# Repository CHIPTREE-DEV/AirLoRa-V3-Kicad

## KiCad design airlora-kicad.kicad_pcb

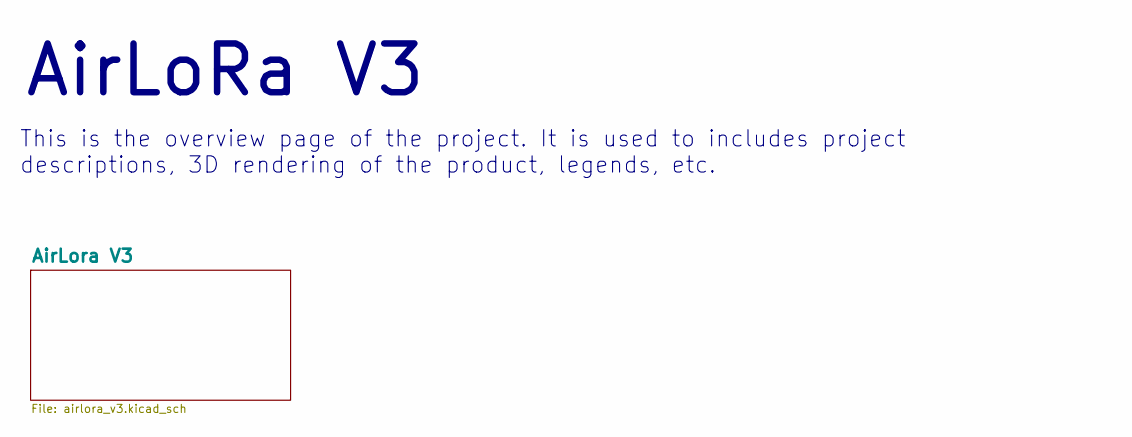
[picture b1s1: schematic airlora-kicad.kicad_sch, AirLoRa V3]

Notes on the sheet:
This is the overview page of the project. It is used to includes project descriptions, 3D rendering of the product, legends, etc.
${TITLE}

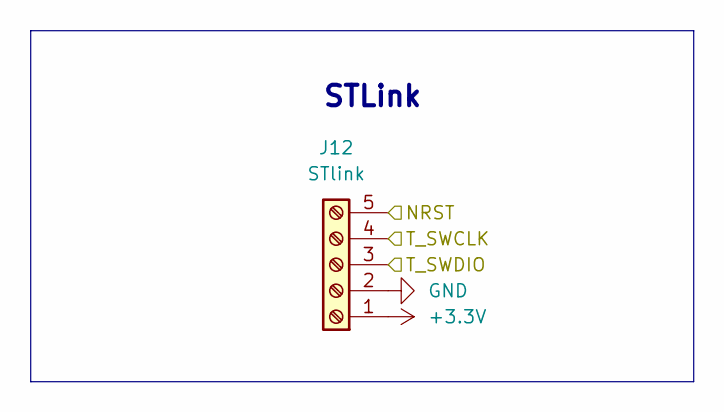
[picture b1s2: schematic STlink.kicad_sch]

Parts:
J12: STlink; JST_XH_B5B-XH-A_1x05_P2.50mm_Vertical

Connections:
+3.3V: J12.1; also elsewhere on the board
/AirLora V3/MCU/NRST: J12.5; also elsewhere on the board
/AirLora V3/MCU/T_SWCLK: J12.4; also elsewhere on the board
/AirLora V3/MCU/T_SWDIO: J12.3; also elsewhere on the board
GND: J12.2; also elsewhere on the board

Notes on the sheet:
STLink

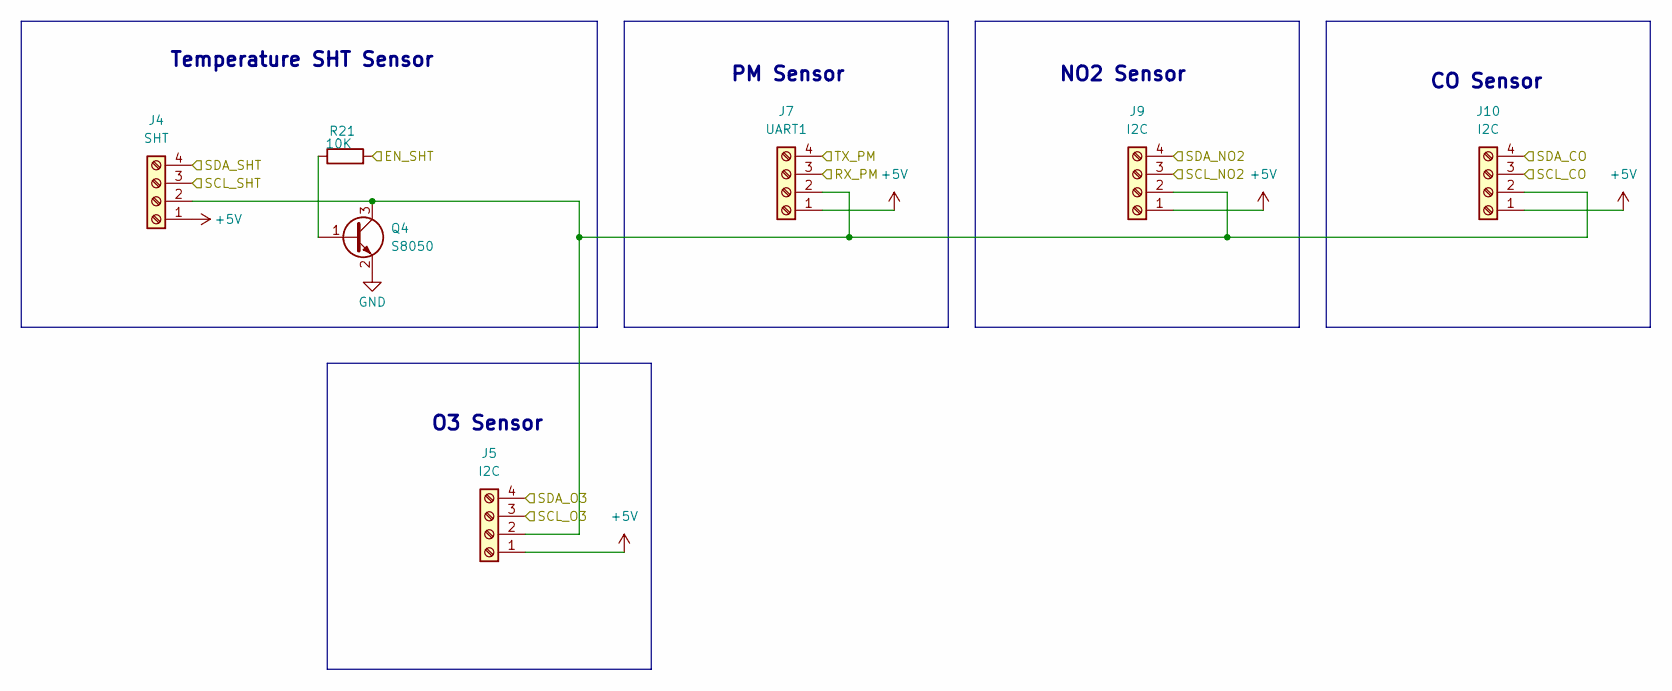
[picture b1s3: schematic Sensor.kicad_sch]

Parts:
J4: SHT; JST_XH_B4B-XH-A_1x04_P2.50mm_Vertical
J5, J9, J10: I2C; Molex_CLIK-Mate_502443-0470_1x04-1MP_P2.00mm_Vertical
J7: UART1; Molex_CLIK-Mate_502443-0470_1x04-1MP_P2.00mm_Vertical
Q4: S8050; SOT-23
R21: 10K; R_0402_1005Metric

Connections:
+5V: J4.1, J5.1, J7.1, J9.1, J10.1; also elsewhere on the board
/AirLora V3/MCU/PB3: R21.2; also elsewhere on the board
/AirLora V3/MCU/SCL2: J4.3, J5.3, J9.3, J10.3; also elsewhere on the board
/AirLora V3/MCU/SDA2: J4.4, J5.4, J9.4, J10.4; also elsewhere on the board
/AirLora V3/MCU/UART1_RX: J7.4; also elsewhere on the board
/AirLora V3/MCU/UART1_TX: J7.3; also elsewhere on the board
GND: Q4.2 (E); also elsewhere on the board
unnamed: J4.2, J5.2, J7.2, J9.2, J10.2, Q4.3 (C)
unnamed: Q4.1 (B), R21.1

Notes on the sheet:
O3 Sensor
NO2 Sensor
PM Sensor
Temperature SHT Sensor
CO Sensor

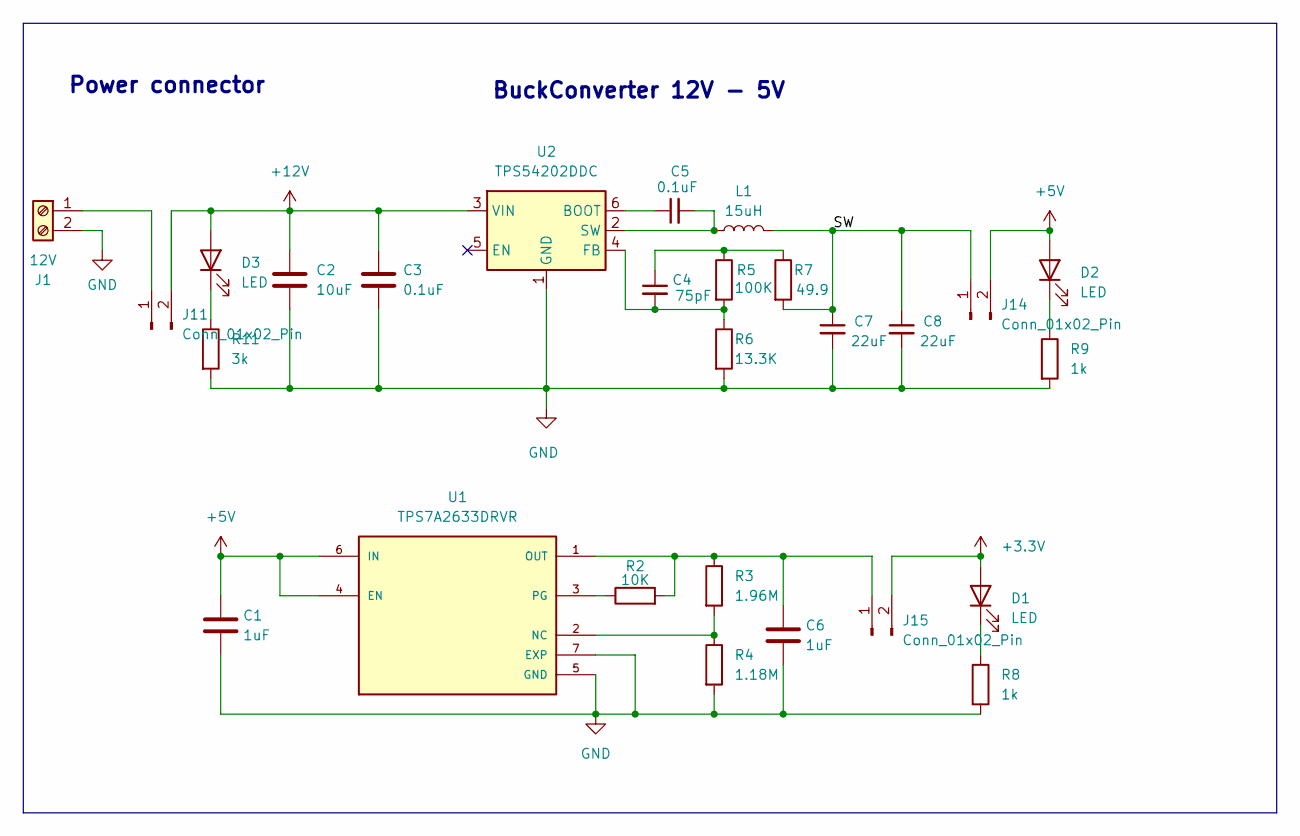
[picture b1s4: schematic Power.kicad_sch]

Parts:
C1, C6: 1uF; C_0805_2012Metric
C2: 10uF; C_1206_3216Metric
C3: 0.1uF; C_0603_1608Metric
C4: 75pF; C_0402_1005Metric
C5: 0.1uF; C_0402_1005Metric
C7, C8: 22uF; C_1206_3216Metric
D1, D2, D3: LED; LED_0603_1608Metric_Pad1.05x0.95mm_HandSolder
J1: 12V; PhoenixContact_MCV_1,5_2-G-3.5_1x02_P3.50mm_Vertical
J11, J14, J15: Conn_01x02_Pin; PinHeader_1x02_P2.54mm_Vertical
L1: 15uH; L_Vishay_IHLP-2020
R2: 10K; R_0402_1005Metric
R3: 1.96M; R_0402_1005Metric
R4: 1.18M; R_0402_1005Metric
R5: 100K; R_0402_1005Metric
R6: 13.3K; R_0402_1005Metric
R7: 49.9; R_0402_1005Metric
R8, R9: 1k; R_0402_1005Metric
R11: 3k; R_0402_1005Metric
U1: TPS7A2633DRVR; LCSC C2876256
U2: TPS54202DDC; SOT-23-6; LCSC C191884

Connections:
+3.3V: D1.2 (A), J15.2; also elsewhere on the board
+5V: C1.1, D2.2 (A), J14.2, U1.4 (EN), U1.6 (IN); also elsewhere on the board
+12V: C2.1, C3.1, D3.2 (A), J11.2, U2.3 (VIN)
/AirLora V3/Power/SW: C7.1, C8.1, J14.1, L1.2, R7.2
GND: C1.2, C2.2, C3.2, C6.2, C7.2, C8.2, J1.2, R4.2, R6.2, R8.2, R9.2, R11.2, U1.5 (GND), U1.7 (EXP), U2.1 (GND); also elsewhere on the board
unnamed: C4.1, R5.1, R7.1
unnamed: D1.1 (K), R8.1
unnamed: D2.1 (K), R9.1
unnamed: D3.1 (K), R11.1
unnamed: J1.1, J11.1
unnamed: C6.1, J15.1, R2.2, R3.1, U1.1 (OUT)
unnamed: R3.2, R4.1, U1.2 (NC)
unnamed: R2.1, U1.3 (PG)
unnamed: C5.1, U2.6 (BOOT)
unnamed: C4.2, R5.2, R6.1, U2.4 (FB)
unnamed: C5.2, L1.1, U2.2 (SW)

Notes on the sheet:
BuckConverter 12V - 5V
Power connector

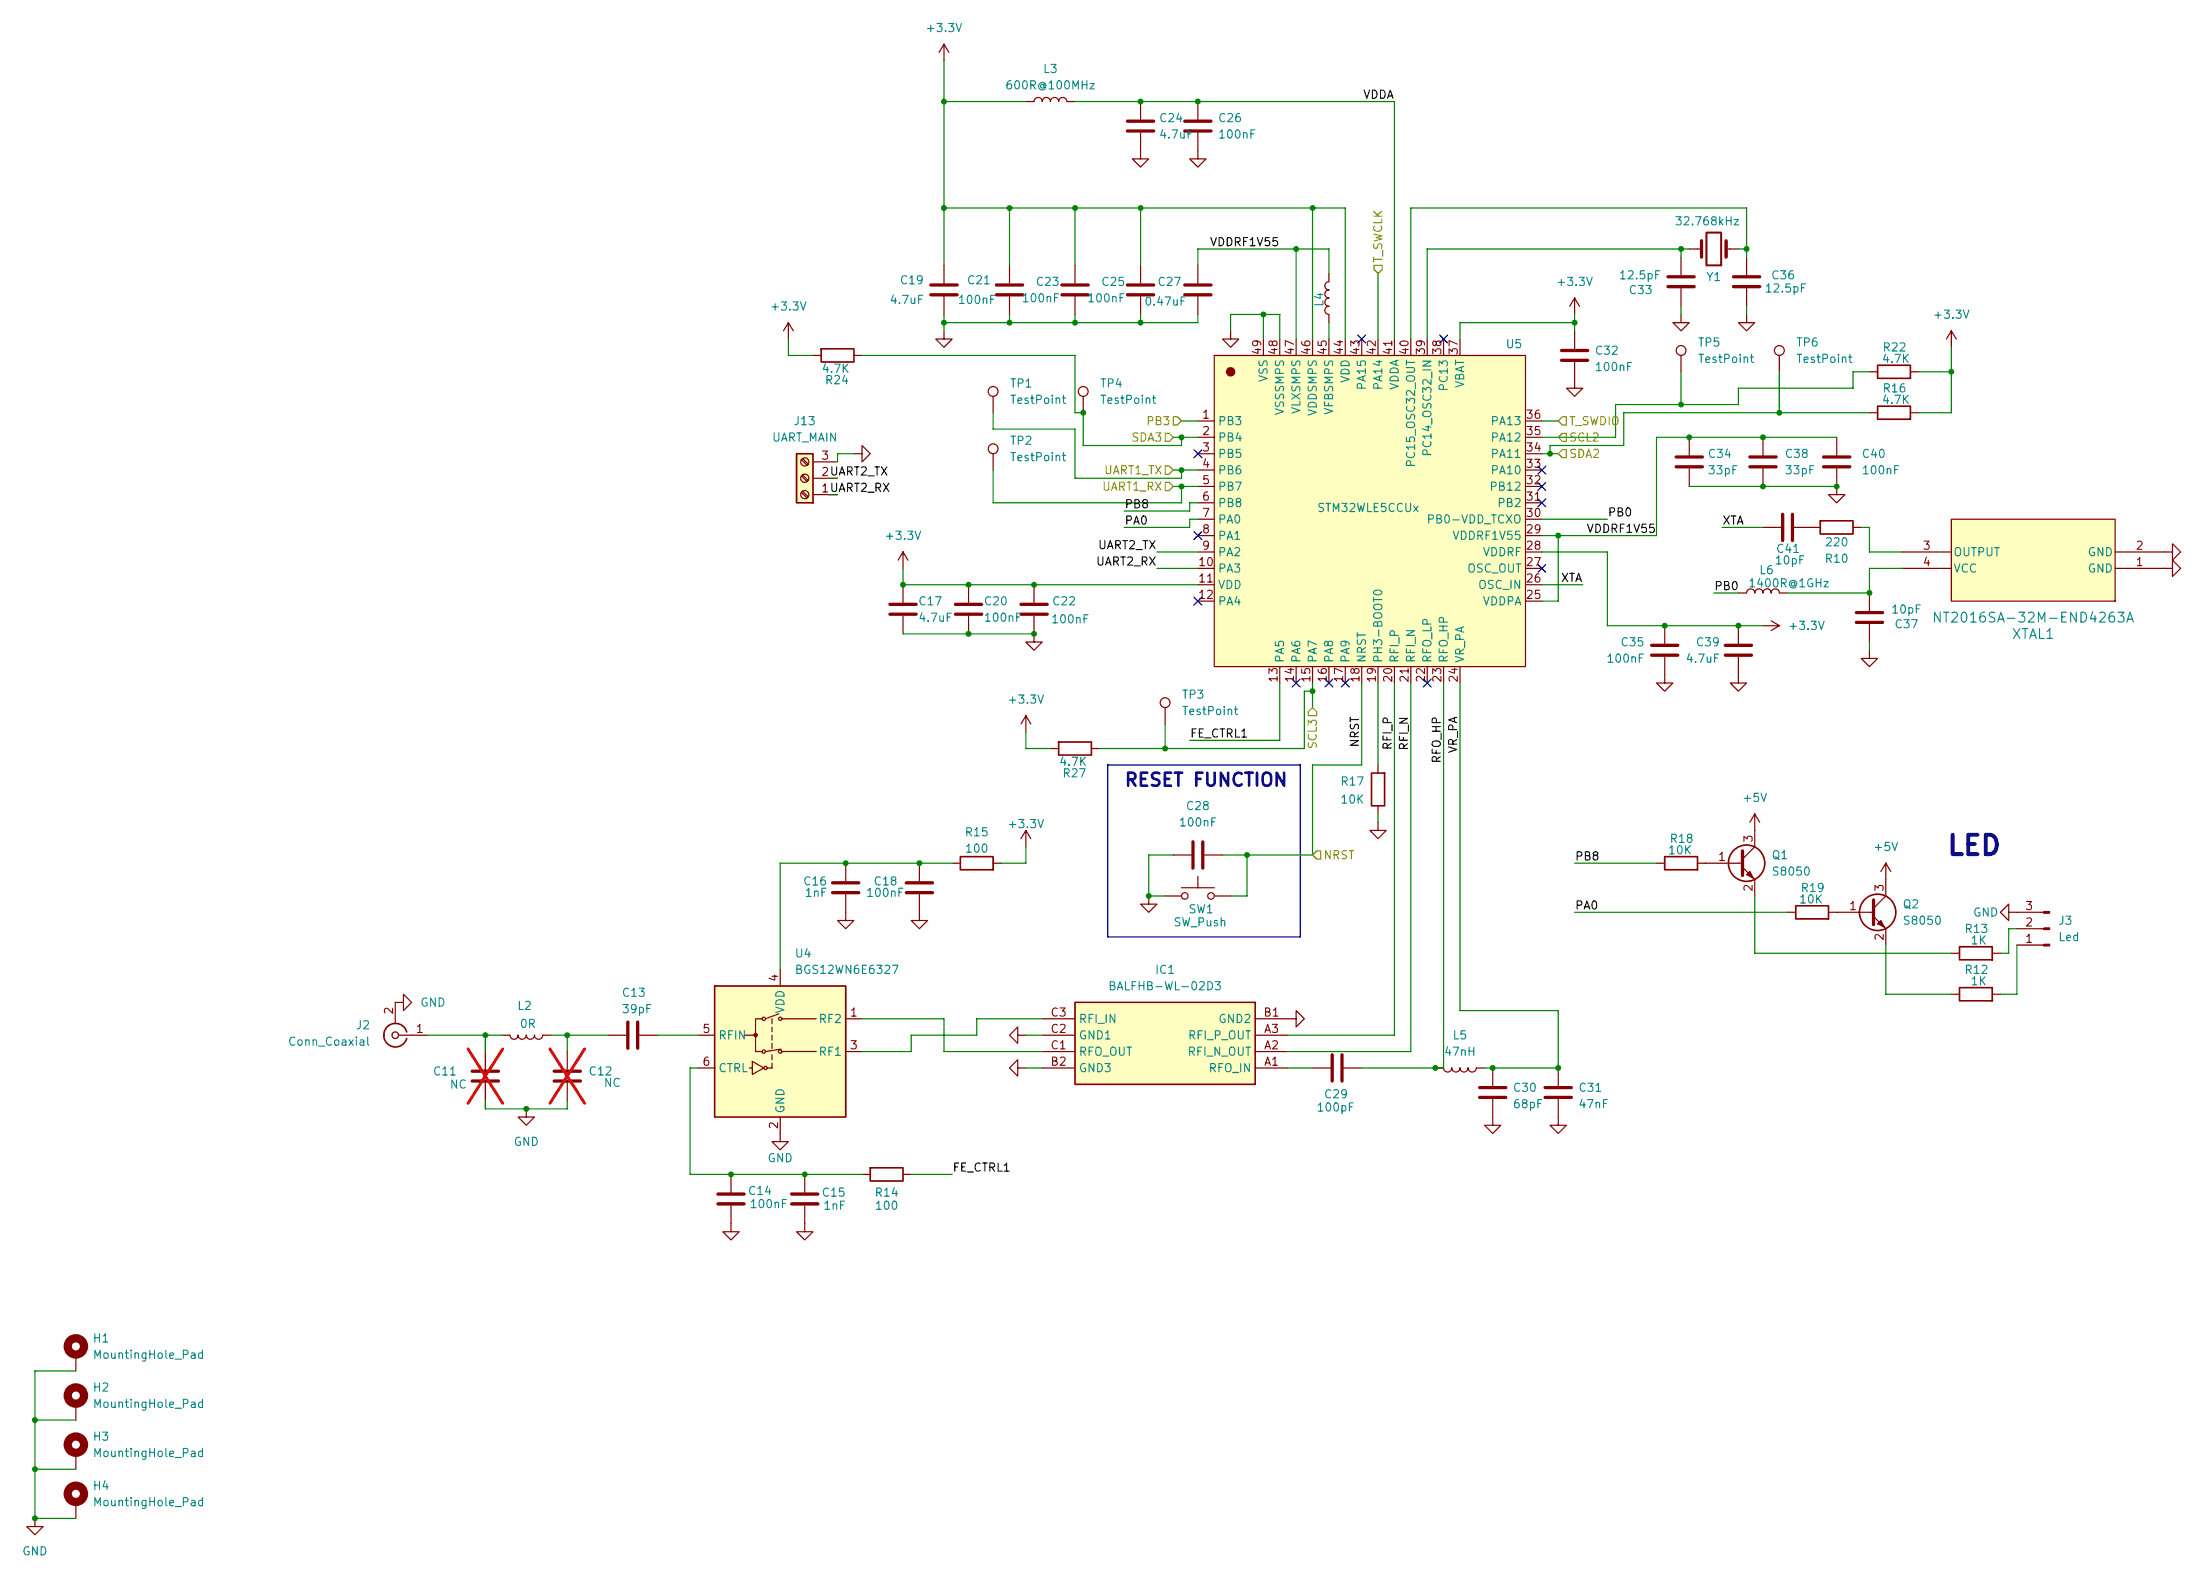
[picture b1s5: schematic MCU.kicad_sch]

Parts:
C11, C12: NC; C_0402_1005Metric; not fitted
C13: 39pF; C_0402_1005Metric
C14, C18, C20, C21, C22, C23, C25, C26, C28, C32, C35, C40: 100nF; C_0402_1005Metric
C15, C16: 1nF; C_0402_1005Metric
C17, C39: 4.7uF; C_0603_1608Metric
C19, C24: 4.7uF; C_0402_1005Metric
C27: 0.47uF; C_0402_1005Metric
C29: 100pF; C_0402_1005Metric
C30: 68pF; C_0402_1005Metric
C31: 47nF; C_0402_1005Metric
C33, C36: 12.5pF; C_0402_1005Metric
C34, C38: 33pF; C_0402_1005Metric
C37, C41: 10pF; C_0402_1005Metric
H1, H2, H3, H4: MountingHole_Pad; MountingHole_3mm_Pad_Via
IC1: BALFHB-WL-02D3; BALFHBWL05D3; Manufacturer_Part_Number BALFHB-WL-05D3; Mouser Part Number 511-BALFHB-WL-05D3
J2: Conn_Coaxial; SMA_Amphenol_132134-11_Vertical
J3: Led; JST_XH_B3B-XH-A_1x03_P2.50mm_Vertical
J13: UART_MAIN; JST_XH_B3B-XH-A_1x03_P2.50mm_Vertical
L2: 0R; L_0402_1005Metric
L3: 600R@100MHz; L_0402_1005Metric
L4: 15uH; C_0805_2012Metric
L5: 47nH; L_0402_1005Metric
L6: 1400R@1GHz; L_0402_1005Metric
Q1, Q2: S8050; SOT-23
R10: 220; R_0402_1005Metric
R12, R13: 1K; R_0603_1608Metric
R14, R15: 100; R_0402_1005Metric
R16, R22, R24, R27: 4.7K; R_0402_1005Metric
R17, R18, R19: 10K; R_0402_1005Metric
SW1: SW_Push; SW_Tactile_SPST_Angled_PTS645Vx39-2LFS
TP1, TP2, TP3, TP4, TP5, TP6: TestPoint; TestPoint_Loop_D1.80mm_Drill1.0mm_Beaded
U4: BGS12WN6E6327; BGS12SN6E6327XTSA1
U5: STM32WLE5CCUx; QFN-48-1EP_7x7mm_P0.5mm_EP5.6x5.6mm
XTAL1: NT2016SA-32M-END4263A; NT2016SA-32M-END4263A_NDK
Y1: 32.768kHz; XTAL_NX2012SA-32.768K-STD-MUB-1

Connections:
+3.3V: C17.1, C19.1, C20.1, C21.2, C22.2, C23.1, C25.1, C32.1, C35.1, C39.1, L3.1, R15.2, R16.2, R22.2, R24.2, R27.2, U5.11 (VDD), U5.28 (VDDRF), U5.37 (VBAT), U5.44 (VDD), U5.46 (VDDSMPS); also elsewhere on the board
+5V: Q1.3 (C), Q2.3 (C); also elsewhere on the board
/AirLora V3/MCU/FE_CTRL1: R14.1, U5.13 (PA5)
/AirLora V3/MCU/NRST: C28.2, SW1.2, U5.18 (NRST); also elsewhere on the board
/AirLora V3/MCU/PA0: R19.1, U5.7 (PA0)
/AirLora V3/MCU/PB0: L6.1, U5.30 (PB0-VDD_TCXO)
/AirLora V3/MCU/PB3: U5.1 (PB3); also elsewhere on the board
/AirLora V3/MCU/PB8: R18.1, U5.6 (PB8)
/AirLora V3/MCU/RFI_N: IC1.A2 (RFI_N_OUT), U5.21 (RFI_N)
/AirLora V3/MCU/RFI_P: IC1.A3 (RFI_P_OUT), U5.20 (RFI_P)
/AirLora V3/MCU/RFO_HP: C29.2, L5.2, U5.23 (RFO_HP)
/AirLora V3/MCU/SCL2: R22.1, TP5.1, U5.35 (PA12); also elsewhere on the board
/AirLora V3/MCU/SCL3: R27.1, TP3.1, U5.15 (PA7)
/AirLora V3/MCU/SDA2: R16.1, TP6.1, U5.34 (PA11); also elsewhere on the board
/AirLora V3/MCU/SDA3: R24.1, TP4.1, U5.2 (PB4)
/AirLora V3/MCU/T_SWCLK: U5.42 (PA14); also elsewhere on the board
/AirLora V3/MCU/T_SWDIO: U5.36 (PA13); also elsewhere on the board
/AirLora V3/MCU/UART1_RX: TP2.1, U5.5 (PB7); also elsewhere on the board
/AirLora V3/MCU/UART1_TX: TP1.1, U5.4 (PB6); also elsewhere on the board
/AirLora V3/MCU/UART2_RX: J13.1, U5.10 (PA3)
/AirLora V3/MCU/UART2_TX: J13.2, U5.9 (PA2)
/AirLora V3/MCU/VDDA: C24.1, C26.1, L3.2, U5.41 (VDDA)
/AirLora V3/MCU/VDDRF1V55: C27.1, C34.1, C38.1, C40.1, L4.2, U5.25 (VDDPA), U5.29 (VDDRF1V55), U5.47 (VLXSMPS)
/AirLora V3/MCU/VR_PA: C30.1, C31.1, L5.1, U5.24 (VR_PA)
/AirLora V3/MCU/XTA: C41.1, U5.26 (OSC_IN)
GND: C11.1, C12.1, C14.2, C15.2, C16.1, C17.2, C18.1, C19.2, C20.2, C21.1, C22.1, C23.2, C24.2, C25.2, C26.2, C27.2, C28.1, C30.2, C31.2, C32.2, C33.2, C34.2, C35.2, C36.1, C37.2, C38.2, C39.2, C40.2, H1.1, H2.1, H3.1, H4.1, IC1.B1 (GND2), IC1.B2 (GND3), IC1.C2 (GND1), J2.2 (Ext), J3.3, J13.3, R17.1, SW1.1, U4.2 (GND), U5.48 (VSSSMPS), U5.49 (VSS), XTAL1.1 (GND), XTAL1.2 (GND); also elsewhere on the board
unnamed: C12.2, C13.2, L2.1
unnamed: C41.2, R10.2
unnamed: IC1.C3 (RFI_IN), U4.3 (RF1)
unnamed: C29.1, IC1.A1 (RFO_IN)
unnamed: IC1.C1 (RFO_OUT), U4.1 (RF2)
unnamed: C11.2, J2.1 (In), L2.2
unnamed: J3.1, R12.2
unnamed: J3.2, R13.2
unnamed: Q1.1 (B), R18.2
unnamed: Q1.2 (E), R13.1
unnamed: Q2.1 (B), R19.2
unnamed: Q2.2 (E), R12.1
unnamed: C14.1, C15.1, R14.2, U4.6 (CTRL)
unnamed: C13.1, U4.5 (RFIN)
unnamed: C16.2, C18.2, R15.1, U4.4 (VDD)
unnamed: C33.1, U5.39 (PC14_OSC32_IN), Y1.2
unnamed: C36.2, U5.40 (PC15_OSC32_OUT), Y1.1
unnamed: R17.2, U5.19 (PH3-BOOT0)
unnamed: L4.1, U5.45 (VFBSMPS)
unnamed: R10.1, XTAL1.3 (OUTPUT)
unnamed: C37.1, L6.2, XTAL1.4 (VCC)

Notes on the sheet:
RESET FUNCTION
LED

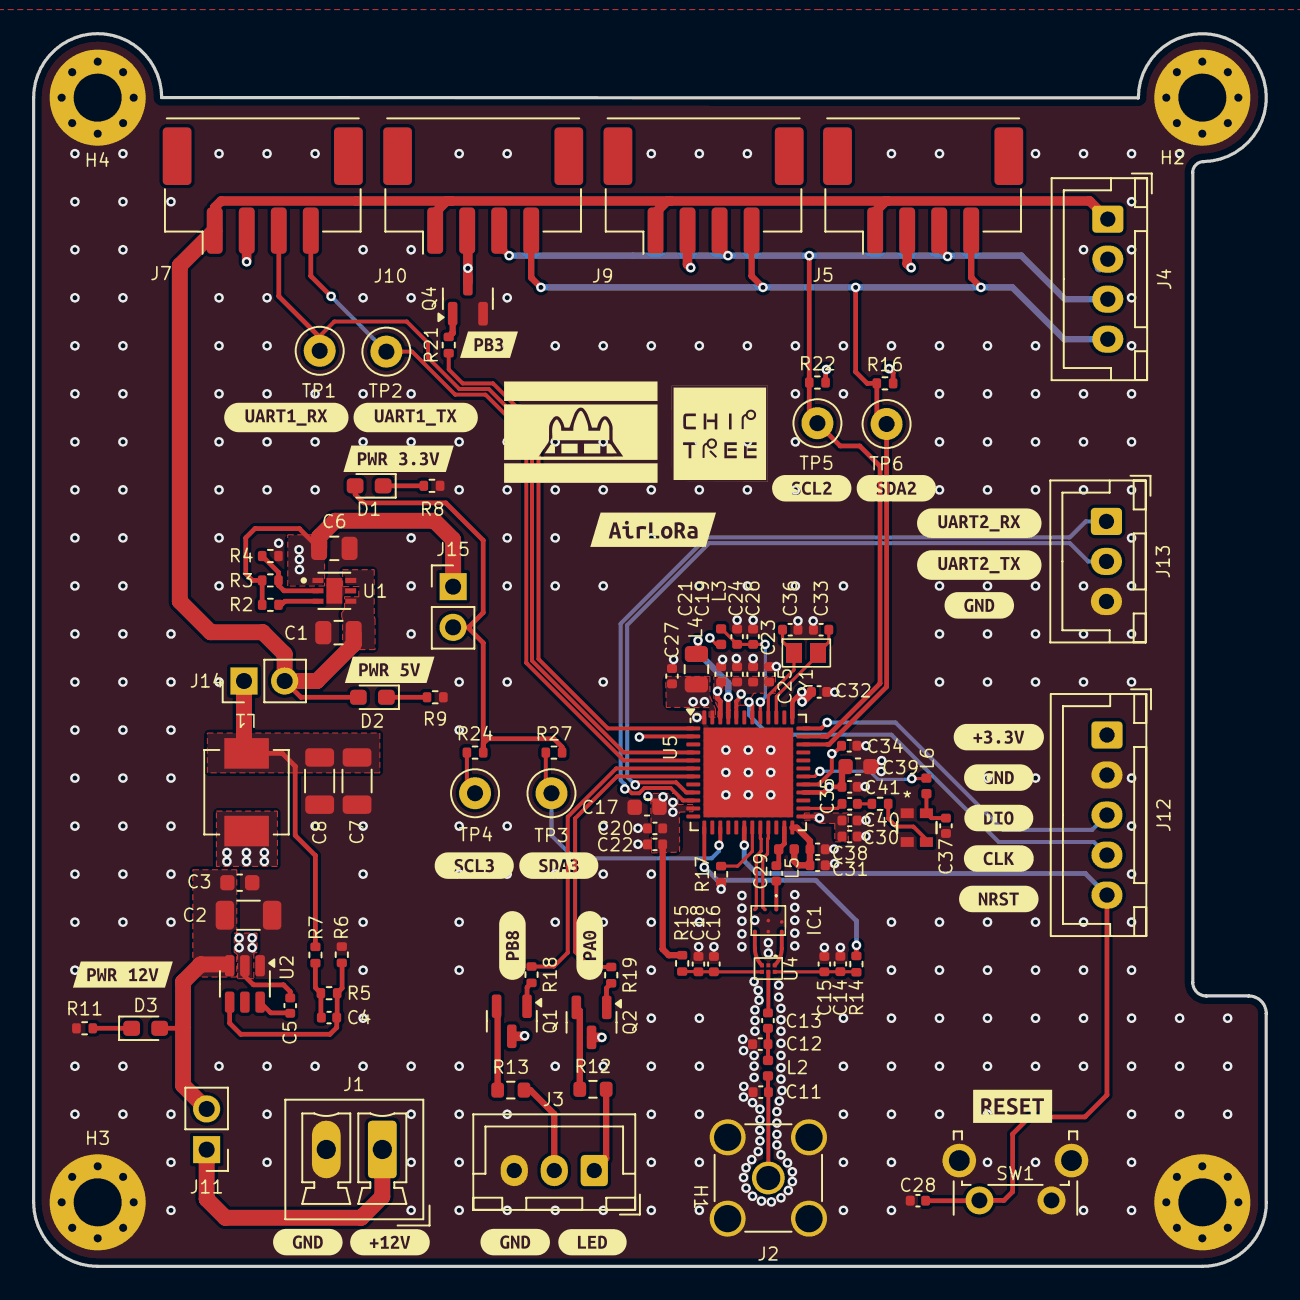
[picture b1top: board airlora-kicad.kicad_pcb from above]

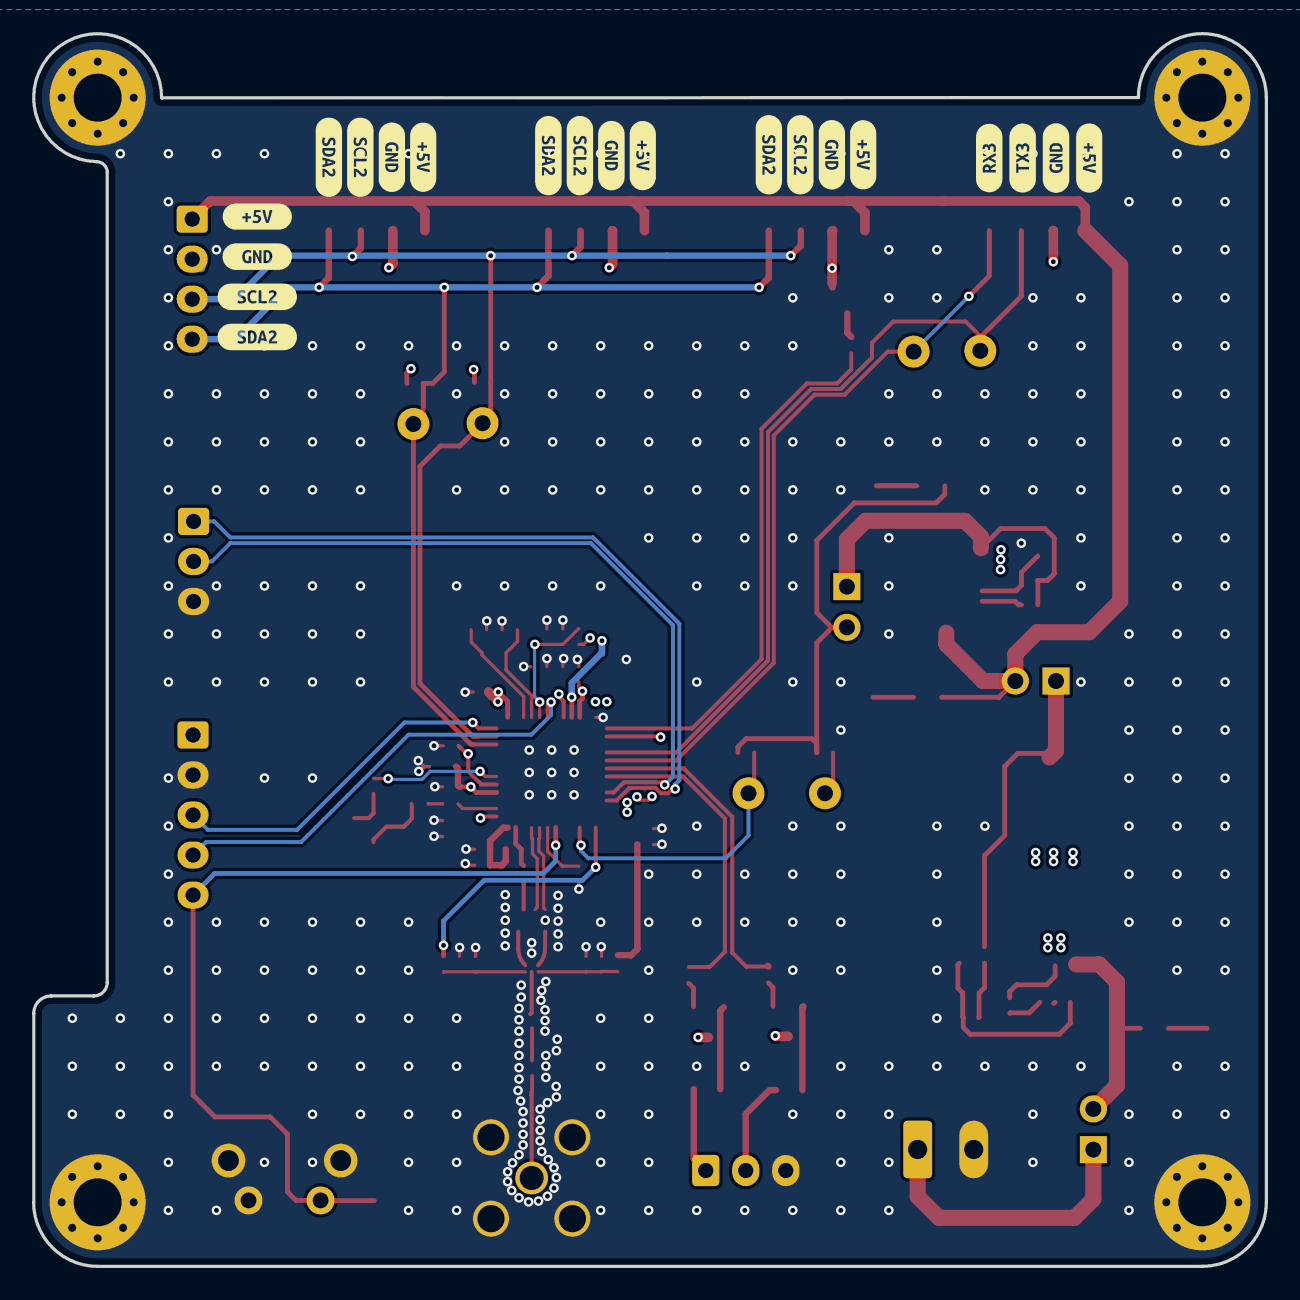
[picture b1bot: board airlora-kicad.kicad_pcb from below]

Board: 4 copper layers, 77.0 x 77.0 mm, 150 parts (20 on the bottom side), 62 nets.

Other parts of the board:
kibuzzard-66A700A1: G***; kibuzzard-66A700A1
kibuzzard-66A704F7: G***; kibuzzard-66A704F7
kibuzzard-66A704FE, kibuzzard-66A704FE#2: G***; kibuzzard-66A704FE
kibuzzard-66A705CB: G***; kibuzzard-66A705CB
kibuzzard-66A705D3: G***; kibuzzard-66A705D3
kibuzzard-66A7008A: G***; kibuzzard-66A7008A
kibuzzard-66A7052C: G***; kibuzzard-66A7052C
kibuzzard-66A7121E: G***; kibuzzard-66A7121E
kibuzzard-66A7130C: G***; kibuzzard-66A7130C
kibuzzard-66A47256: G***; kibuzzard-66A47256
kibuzzard-66A70081: G***; kibuzzard-66A70081
kibuzzard-66A70091: G***; kibuzzard-66A70091
kibuzzard-66A70098: G***; kibuzzard-66A70098
kibuzzard-66A70504, kibuzzard-66A70504#2: G***; kibuzzard-66A70504
kibuzzard-66A70534: G***; kibuzzard-66A70534
kibuzzard-66A71226: G***; kibuzzard-66A71226
kibuzzard-66A71314: G***; kibuzzard-66A71314
kibuzzard-66A71938: G***; kibuzzard-66A71938
kibuzzard-6690D08F: G***; kibuzzard-6690D08F
kibuzzard-66763AB2: G***; kibuzzard-66763AB2
kibuzzard-66763ACD: G***; kibuzzard-66763ACD
kibuzzard-667540EB, kibuzzard-667540EB#2, kibuzzard-667540EB#3, kibuzzard-667540EB#4, kibuzzard-667540EB#5: G***; kibuzzard-667540EB
kibuzzard-667541A7: G***; kibuzzard-667541A7
kibuzzard-667541BE: G***; kibuzzard-667541BE
kibuzzard-667541C9: G***; kibuzzard-667541C9
kibuzzard-6679349C: G***; kibuzzard-6679349C
kibuzzard-66752922, kibuzzard-66752922#2, kibuzzard-66752922#3, kibuzzard-66752922#4, kibuzzard-66752922#5, kibuzzard-66752922#6, kibuzzard-66752922#7, kibuzzard-66752922#8, kibuzzard-66752922#9: G***; kibuzzard-66752922
kibuzzard-66752939: G***; kibuzzard-66752939
kibuzzard-66752971: G***; kibuzzard-66752971
kibuzzard-66752981: G***; kibuzzard-66752981
kibuzzard-66753395: G***; kibuzzard-66753395
kibuzzard-66754176: G***; kibuzzard-66754176

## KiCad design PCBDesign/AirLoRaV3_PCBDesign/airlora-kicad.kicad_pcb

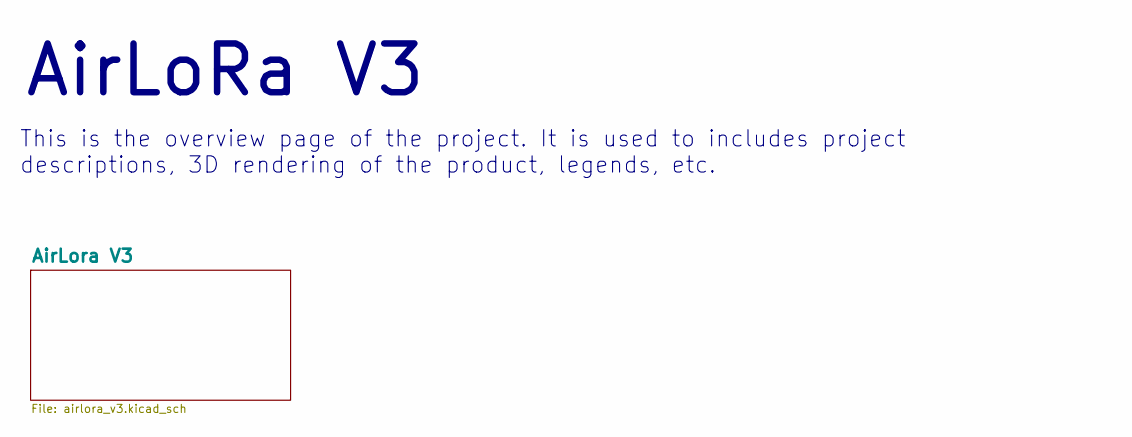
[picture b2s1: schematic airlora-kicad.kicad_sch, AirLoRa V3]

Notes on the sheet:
This is the overview page of the project. It is used to includes project descriptions, 3D rendering of the product, legends, etc.
${TITLE}

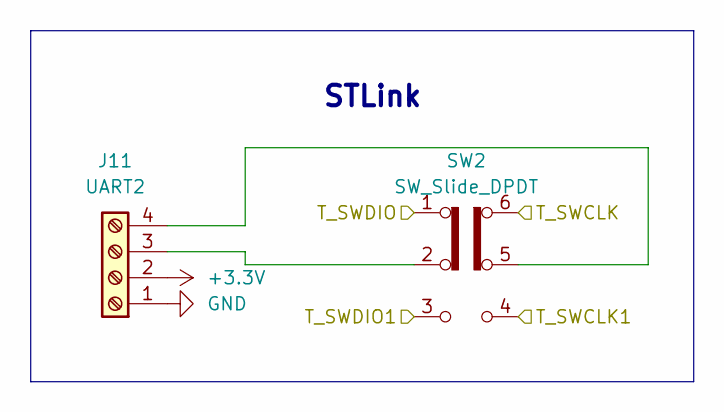
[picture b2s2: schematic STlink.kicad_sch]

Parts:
J11: UART2; JST_XH_B4B-XH-A_1x04_P2.50mm_Vertical
SW2: SW_Slide_DPDT; SW_E-Switch_EG1271_SPDT

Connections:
+3.3V: J11.2; also elsewhere on the board
/AirLora V3/MCU Sub/SW_CLK: SW2.4 (A); also elsewhere on the board
/AirLora V3/MCU Sub/SW_DIO: SW2.3 (C); also elsewhere on the board
/AirLora V3/MCU/T_SWCLK: SW2.6 (C); also elsewhere on the board
/AirLora V3/MCU/T_SWDIO: SW2.1 (A); also elsewhere on the board
GND: J11.1; also elsewhere on the board
unnamed: J11.3, SW2.2 (B)
unnamed: J11.4, SW2.5 (B)

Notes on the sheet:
STLink

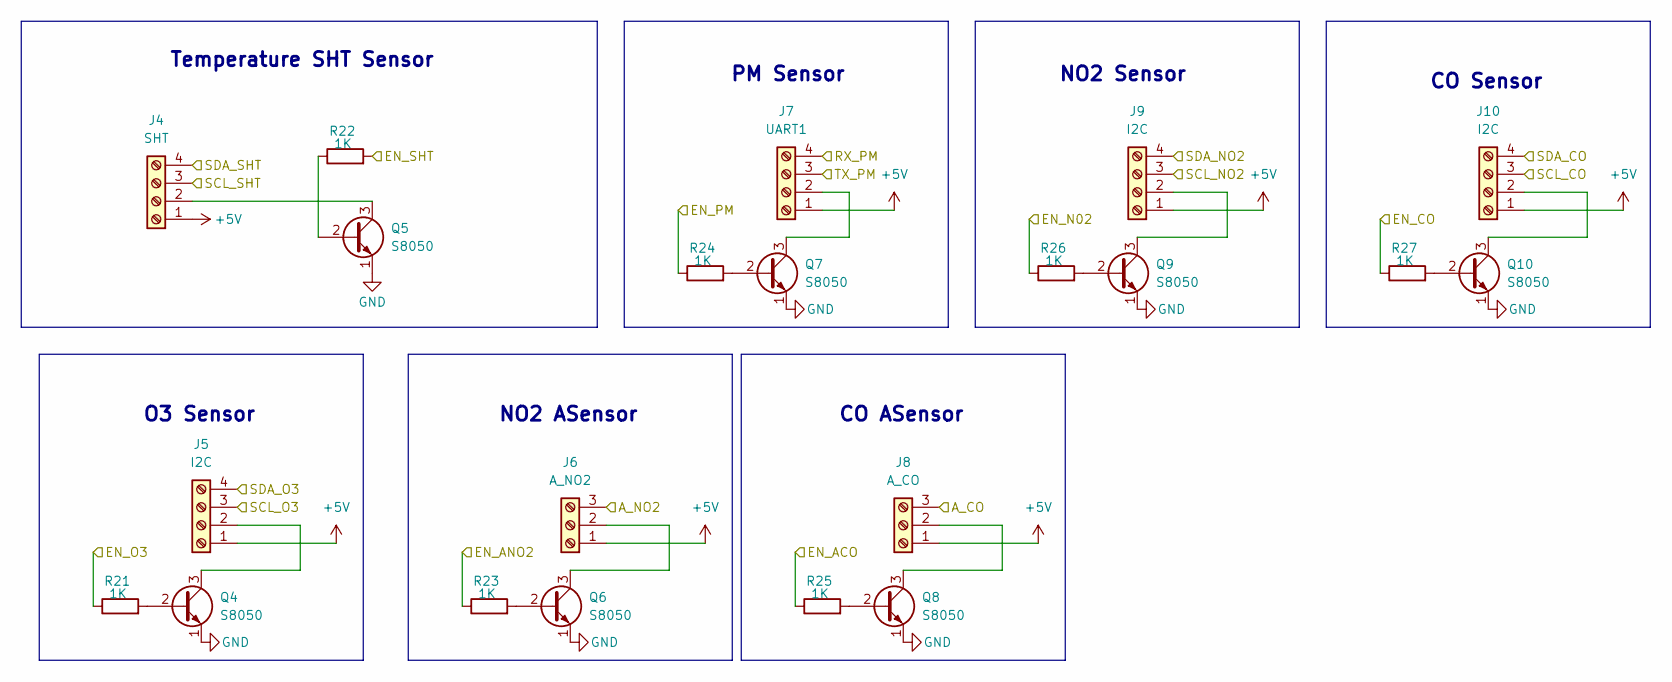
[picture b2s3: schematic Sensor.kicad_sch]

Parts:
J4: SHT; JST_XH_B4B-XH-A_1x04_P2.50mm_Vertical
J5, J9, J10: I2C; Molex_CLIK-Mate_502585-0470_1x04-1MP_P1.50mm_Horizontal
J6: A_NO2; JST_XH_B3B-XH-A_1x03_P2.50mm_Vertical
J7: UART1; Molex_CLIK-Mate_502585-0470_1x04-1MP_P1.50mm_Horizontal
J8: A_CO; JST_XH_B3B-XH-A_1x03_P2.50mm_Vertical
Q4, Q5, Q6, Q7, Q8, Q9, Q10: S8050; SOT-23
R21, R22, R23, R24, R25, R26, R27: 1K; R_0402_1005Metric_Pad0.72x0.64mm_HandSolder

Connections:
+5V: J4.1, J5.1, J6.1, J7.1, J8.1, J9.1, J10.1; also elsewhere on the board
/AirLora V3/MCU Sub/PA4: R25.1; also elsewhere on the board
/AirLora V3/MCU Sub/PA5: R24.1; also elsewhere on the board
/AirLora V3/MCU Sub/PA6: R23.1; also elsewhere on the board
/AirLora V3/MCU Sub/PA7: R22.2; also elsewhere on the board
/AirLora V3/MCU Sub/PA15: R21.1; also elsewhere on the board
/AirLora V3/MCU Sub/PB0: J6.3; also elsewhere on the board
/AirLora V3/MCU Sub/PB1: J8.3; also elsewhere on the board
/AirLora V3/MCU Sub/PB3: R26.1; also elsewhere on the board
/AirLora V3/MCU Sub/PB4: R27.1; also elsewhere on the board
/AirLora V3/MCU Sub/RX3: J7.3; also elsewhere on the board
/AirLora V3/MCU Sub/SCL1: J4.3, J5.3, J9.3, J10.3; also elsewhere on the board
/AirLora V3/MCU Sub/SDA1: J4.4, J5.4, J9.4, J10.4; also elsewhere on the board
/AirLora V3/MCU Sub/TX3: J7.4; also elsewhere on the board
GND: Q4.1 (E), Q5.1 (E), Q6.1 (E), Q7.1 (E), Q8.1 (E), Q9.1 (E), Q10.1 (E); also elsewhere on the board
unnamed: J4.2, Q5.3 (C)
unnamed: J5.2, Q4.3 (C)
unnamed: J6.2, Q6.3 (C)
unnamed: J7.2, Q7.3 (C)
unnamed: J8.2, Q8.3 (C)
unnamed: J9.2, Q9.3 (C)
unnamed: J10.2, Q10.3 (C)
unnamed: Q4.2 (B), R21.2
unnamed: Q5.2 (B), R22.1
unnamed: Q6.2 (B), R23.2
unnamed: Q7.2 (B), R24.2
unnamed: Q8.2 (B), R25.2
unnamed: Q9.2 (B), R26.2
unnamed: Q10.2 (B), R27.2

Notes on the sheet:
O3 Sensor
NO2 Sensor
NO2 ASensor
PM Sensor
Temperature SHT Sensor
CO ASensor
CO Sensor

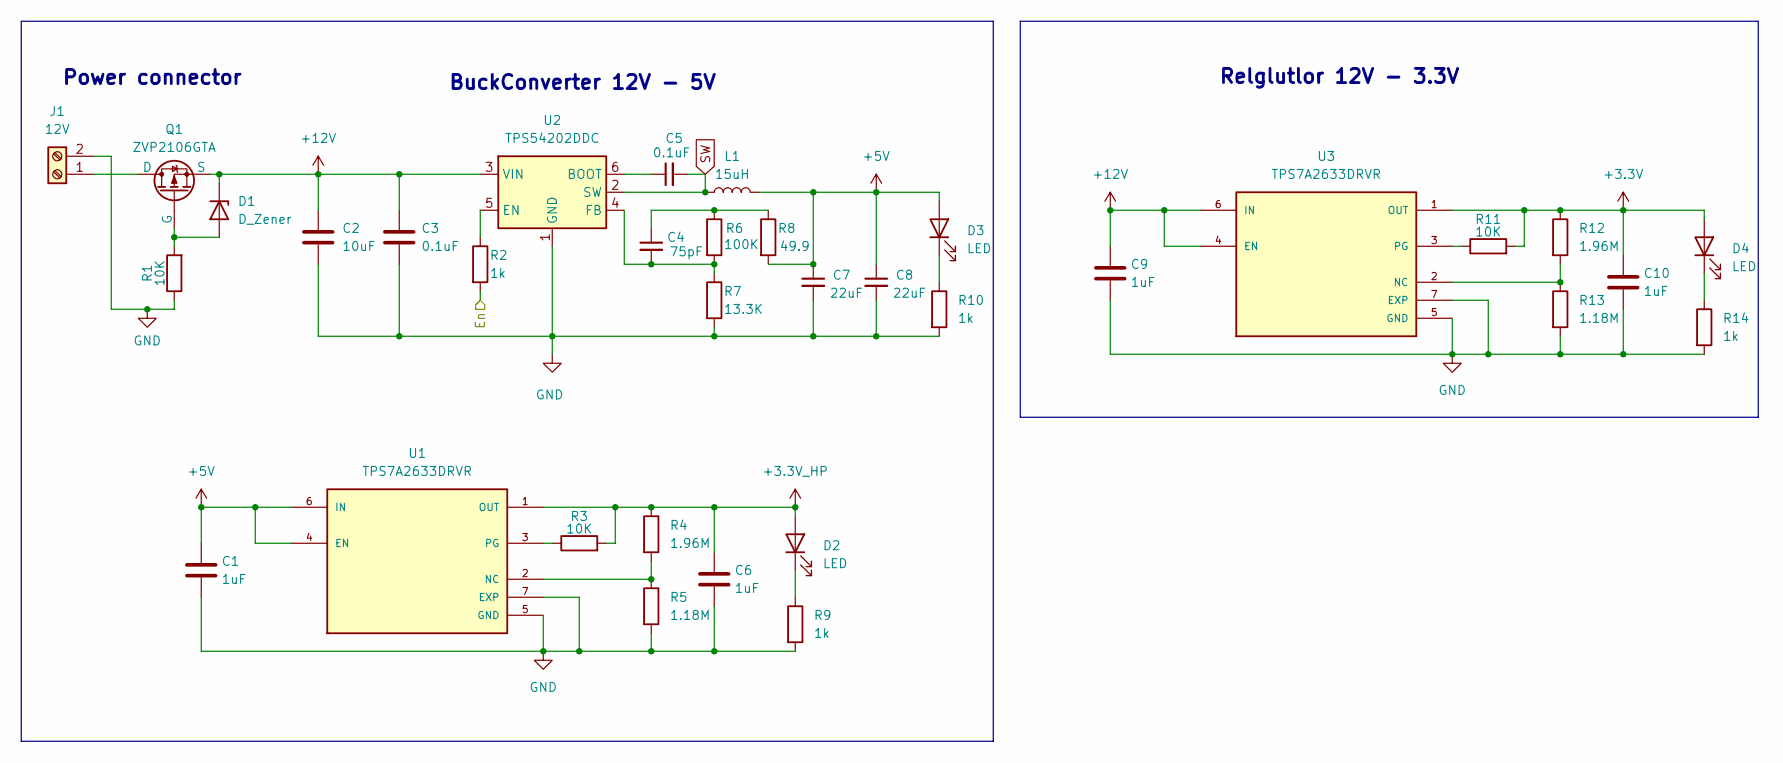
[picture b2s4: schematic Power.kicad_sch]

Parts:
C1, C6, C9, C10: 1uF; C_0805_2012Metric_Pad1.18x1.45mm_HandSolder
C2: 10uF; C_1206_3216Metric_Pad1.33x1.80mm_HandSolder
C3: 0.1uF; C_0603_1608Metric
C4: 75pF; C_0402_1005Metric_Pad0.74x0.62mm_HandSolder
C5: 0.1uF; C_0402_1005Metric_Pad0.74x0.62mm_HandSolder
C7, C8: 22uF; C_1206_3216Metric_Pad1.33x1.80mm_HandSolder
D1: D_Zener; D_SMA_Handsoldering
D2, D3, D4: LED; LED_0603_1608Metric_Pad1.05x0.95mm_HandSolder
J1: 12V; PhoenixContact_MCV_1,5_2-G-3.5_1x02_P3.50mm_Vertical
L1: 15uH; L_Vishay_IHLP-2020
Q1: ZVP2106GTA; SOT-223-3_TabPin2
R1, R3, R11: 10K; R_0402_1005Metric_Pad0.72x0.64mm_HandSolder
R2, R9, R10, R14: 1k; R_0402_1005Metric_Pad0.72x0.64mm_HandSolder
R4, R12: 1.96M; R_0402_1005Metric_Pad0.72x0.64mm_HandSolder
R5, R13: 1.18M; R_0402_1005Metric_Pad0.72x0.64mm_HandSolder
R6: 100K; R_0402_1005Metric_Pad0.72x0.64mm_HandSolder
R7: 13.3K; R_0402_1005Metric_Pad0.72x0.64mm_HandSolder
R8: 49.9; R_0402_1005Metric_Pad0.72x0.64mm_HandSolder
U1, U3: TPS7A2633DRVR; LCSC C2876256
U2: TPS54202DDC; SOT-23-6; LCSC C191884

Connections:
+3.3V: C10.1, D4.2 (A), R11.2, R12.1, U3.1 (OUT); also elsewhere on the board
+3.3V_HP: C6.1, D2.2 (A), R3.2, R4.1, U1.1 (OUT); also elsewhere on the board
+5V: C1.1, C7.1, C8.1, D3.2 (A), L1.2, R8.2, U1.4 (EN), U1.6 (IN); also elsewhere on the board
+12V: C2.1, C3.1, C9.1, D1.1 (K), Q1.3 (S), U2.3 (VIN), U3.4 (EN), U3.6 (IN)
/AirLora V3/MCU/PA3: R2.2; also elsewhere on the board
GND: C1.2, C2.2, C3.2, C6.2, C7.2, C8.2, C9.2, C10.2, J1.2, R1.1, R5.2, R7.2, R9.2, R10.2, R13.2, R14.2, U1.5 (GND), U1.7 (EXP), U2.1 (GND), U3.5 (GND), U3.7 (EXP); also elsewhere on the board
unnamed: C4.1, R6.1, R8.1
unnamed: D1.2 (A), Q1.1 (G), R1.2
unnamed: D2.1 (K), R9.1
unnamed: D3.1 (K), R10.1
unnamed: D4.1 (K), R14.1
unnamed: J1.1, Q1.2 (D)
unnamed: R4.2, R5.1, U1.2 (NC)
unnamed: R3.1, U1.3 (PG)
unnamed: C5.1, U2.6 (BOOT)
unnamed: R2.1, U2.5 (EN)
unnamed: C4.2, R6.2, R7.1, U2.4 (FB)
unnamed: R12.2, R13.1, U3.2 (NC)
unnamed: R11.1, U3.3 (PG)
SW: C5.2, L1.1, U2.2 (SW)

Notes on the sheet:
Relglutlor 12V - 3.3V
BuckConverter 12V - 5V
Power connector
